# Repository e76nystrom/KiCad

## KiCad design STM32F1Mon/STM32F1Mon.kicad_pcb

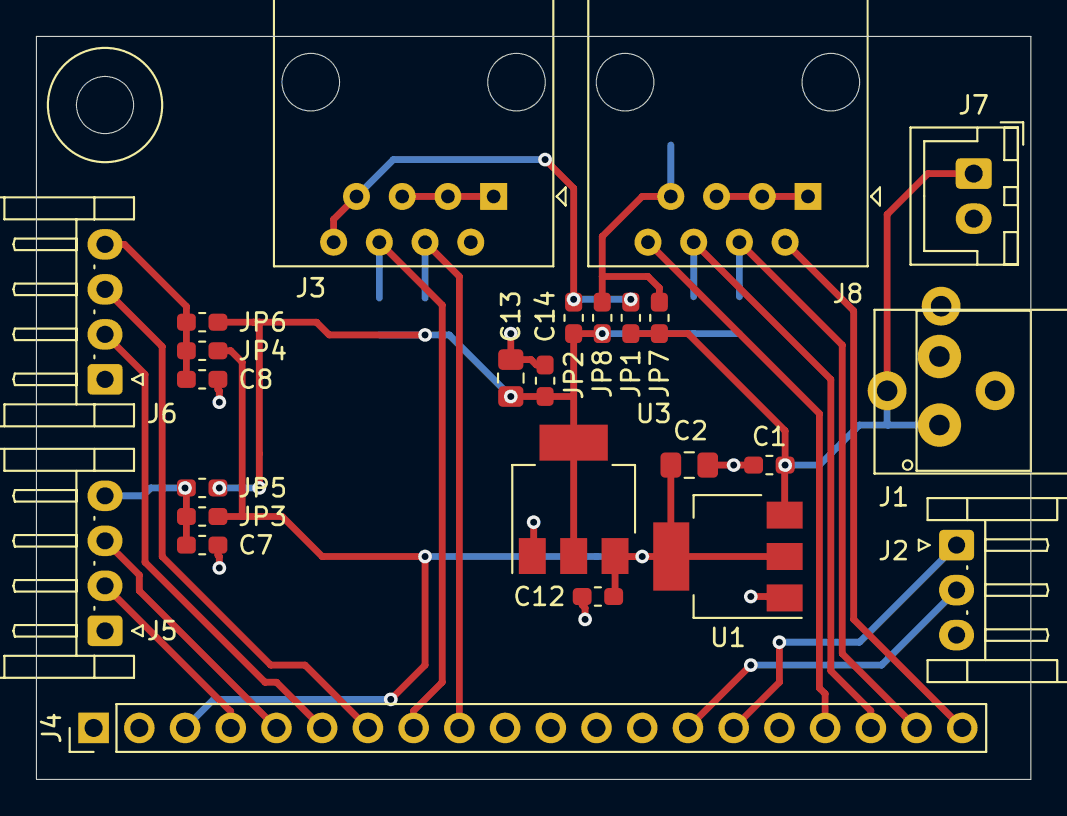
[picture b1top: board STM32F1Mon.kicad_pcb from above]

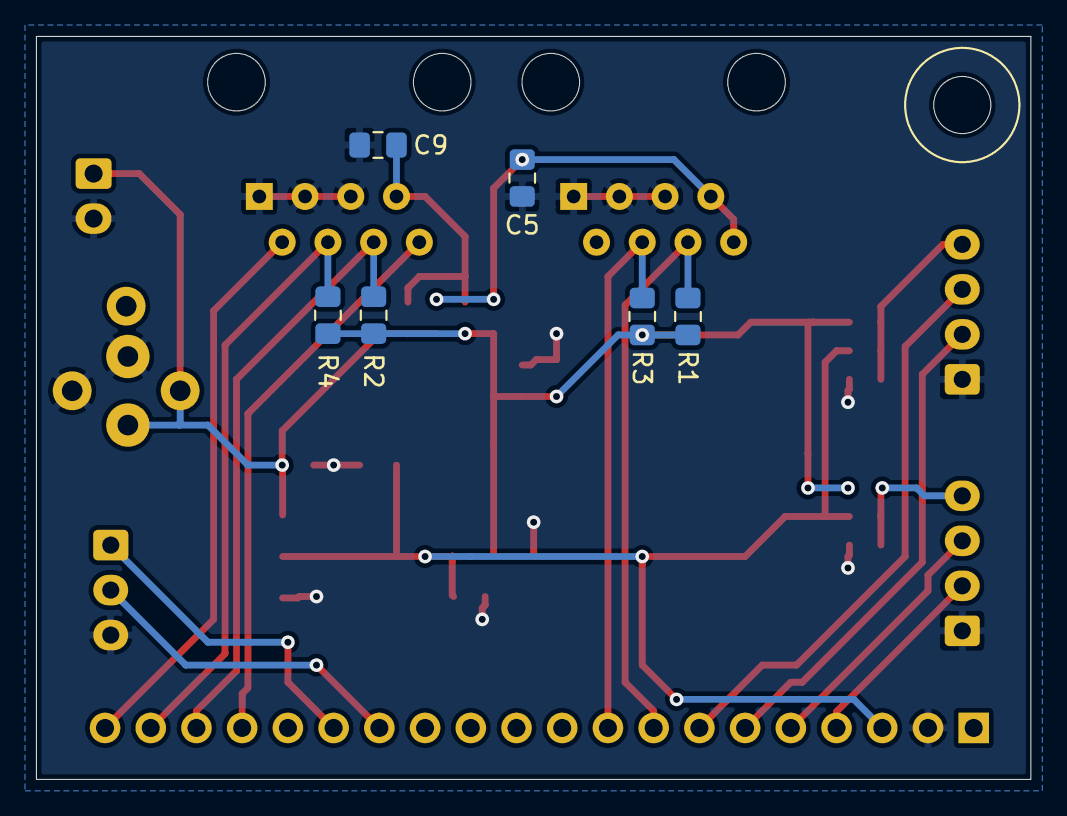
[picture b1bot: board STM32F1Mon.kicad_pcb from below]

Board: 2 copper layers, 55.2 x 41.3 mm, 32 parts (6 on the bottom side), 20 nets.

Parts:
C1, C7, C8, C12, C14: .1uf; C_0603_1608Metric_Pad1.05x0.95mm_HandSolder
C2, C13: 10u; C_0805_2012Metric_Pad1.15x1.40mm_HandSolder
C5, C9: .1; C_0805_2012Metric_Pad1.15x1.40mm_HandSolder
H1: MountingHole; MountingHole _1-8_1-4
J1: PJ-102; PJ-102-3.81mm
J2: Conn_01x03_Female; JST_EH_S3B-EH_1x03_P2.50mm_Horizontal
J3, J8: RJ45; RJ45_Amphenol_54602-x08_Horizontal
J4: Conn_01x20_Male; PinHeader_1x20_P2.54mm_Vertical
J5, J6: Conn_01x04_Female; JST_EH_S4B-EH_1x04_P2.50mm_Horizontal
J7: Conn_01x02; JST_XH_B2B-XH-A_1x02_P2.50mm_Vertical
JP1, JP2, JP3, JP4, JP5, JP6, JP7, JP8: Jumper_NO_Small; R_0603_1608Metric_Pad1.05x0.95mm_HandSolder
R1, R2, R3, R4: R; R_0805_2012Metric_Pad1.15x1.40mm_HandSolder
U1: AP1117-50; SOT-223-3_TabPin2
U3: AP1117-33; SOT-223-3_TabPin2

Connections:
+3V3: C13.1, C14.1, JP2.1, JP5.1, JP6.1, JP8.1, R1.1, R2.1, R3.1, R4.1, U3.2
+5V: C2.1, C12.1, J4.3, JP3.1, JP4.1, U1.2, U3.3
/A9: J2.1, J4.15
/A10: J2.2, J4.14
/B4: J3.4, J4.9, R3.2
/B5: J3.6, J4.8, R1.2
/B6: J4.7, J6.3
/B7: J4.6, J6.2
/B8: J4.5, J5.3
/B9: J4.4, J5.2
/B12: J4.20, J8.2
/B13: J4.19, J8.4, R4.2
/B14: J4.18, J8.6, R2.2
/B15: J4.17, J8.8
/SensorPwr0: C5.1, J3.7, J3.8, JP1.2, JP2.2
/SensorPwr1: C9.1, J8.7, JP7.2, JP8.2
/VA0: C7.2, J5.4, JP3.2, JP5.2
/VA1: C8.2, J6.4, JP4.2, JP6.2
/Vin: C1.1, J1.1, J7.1, JP1.1, JP7.1, U1.3
GND: C1.2, C2.2, C5.2, C7.1, C8.1, C9.2, C12.2, C13.2, C14.2, J1.2, J2.3, J3.1, J3.3, J3.5, J4.2, J5.1, J6.1, J7.2, J8.1, J8.3, J8.5, U1.1, U3.1

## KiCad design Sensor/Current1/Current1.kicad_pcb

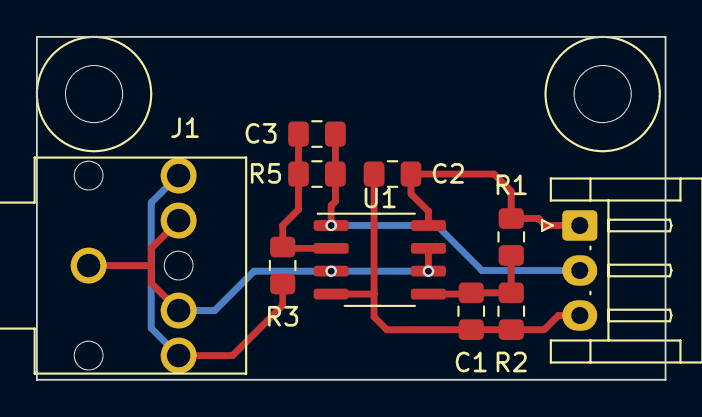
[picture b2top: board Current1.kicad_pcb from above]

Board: 2 copper layers, 34.9 x 19.0 mm, 12 parts (0 on the bottom side), 7 nets.

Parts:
C1: 1uf; C_0805_2012Metric_Pad1.15x1.40mm_HandSolder
C2: .1uf; C_0805_2012Metric_Pad1.15x1.40mm_HandSolder
C3: C; C_0805_2012Metric_Pad1.15x1.40mm_HandSolder
H1, H2: MountingHole; MountingHole _1-8_1-4
J1: STX-3120-5B; AudioJack
J2: Conn_01x03_Male; JST_EH_S3B-EH_1x03_P2.50mm_Horizontal
R1, R2: 10k; R_0805_2012Metric_Pad1.15x1.40mm_HandSolder
R3, R5: R_0805_2012Metric_Pad1.15x1.40mm_HandSolder
U1: OPA2170; SOIC-8_3.9x5.4mm_P1.27mm

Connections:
+3V3: C2.1, J2.1, R1.2, U1.8
/Amp+: J1.1, J1.3, J1.4, U1.3, U1.6, U1.7
/Amp-: C3.2, R3.1, R5.2, U1.2
/Cur+: J1.2, J1.5, R3.2
/Out: C3.1, J2.2, R5.1, U1.1
/Ref: C1.1, R1.1, R2.2, U1.5
GND: C1.2, C2.2, J2.3, R2.1, U1.4

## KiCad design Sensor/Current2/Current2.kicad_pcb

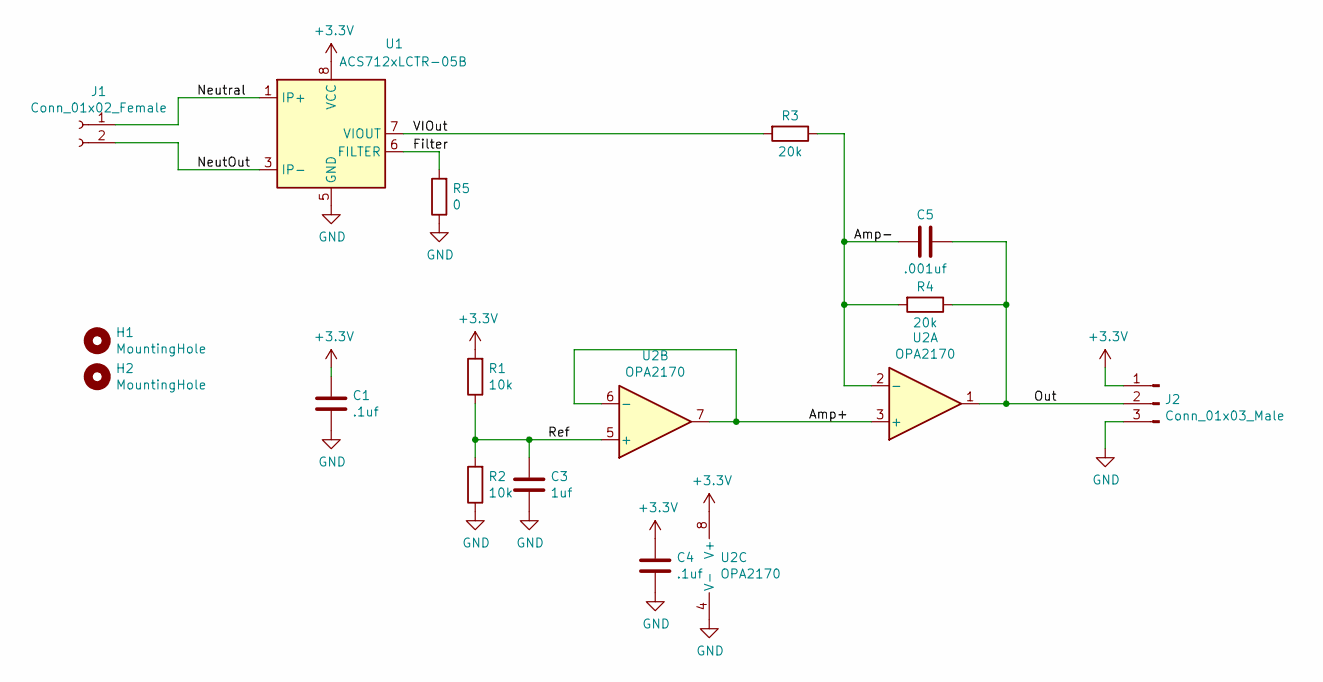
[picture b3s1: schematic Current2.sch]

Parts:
C1, C4: .1uf; C_0805_2012Metric_Pad1.15x1.40mm_HandSolder
C3: 1uf; C_0805_2012Metric_Pad1.15x1.40mm_HandSolder
C5: .001uf; C_0805_2012Metric_Pad1.15x1.40mm_HandSolder
H1, H2: MountingHole; MountingHole _1-8_1-4
J1: Conn_01x02_Female; 2_Pin_5mm
J2: Conn_01x03_Male; JST_EH_S3B-EH_1x03_P2.50mm_Horizontal
R1, R2: 10k; R_0805_2012Metric_Pad1.15x1.40mm_HandSolder
R3, R4: 20k; R_0805_2012Metric_Pad1.15x1.40mm_HandSolder
R5: 0; R_0805_2012Metric_Pad1.15x1.40mm_HandSolder
U1: ACS712xLCTR-05B; SOIC-8_3.9x5.6mm_P1.27mm
U2: OPA2170; SOIC-8_3.9x5.4mm_P1.27mm

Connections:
+3V3: C1.1, C4.1, J2.1, R1.2, U1.8 (VCC), U2.8 (V+)
/Amp+: U2.3 (+), U2.6 (-), U2.7
/Amp-: C5.2, R3.1, R4.2, U2.2 (-)
/Filter: R5.2, U1.6 (FILTER)
/NeutOut: J1.2, U1.3 (IP-), U1.4 (IP-)
/Neutral: J1.1, U1.1 (IP+), U1.2 (IP+)
/Out: C5.1, J2.2, R4.1, U2.1
/Ref: C3.1, R1.1, R2.2, U2.5 (+)
/VIOut: R3.2, U1.7 (VIOUT)
GND: C1.2, C3.2, C4.2, J2.3, R2.1, R5.1, U1.5 (GND), U2.4 (V-)

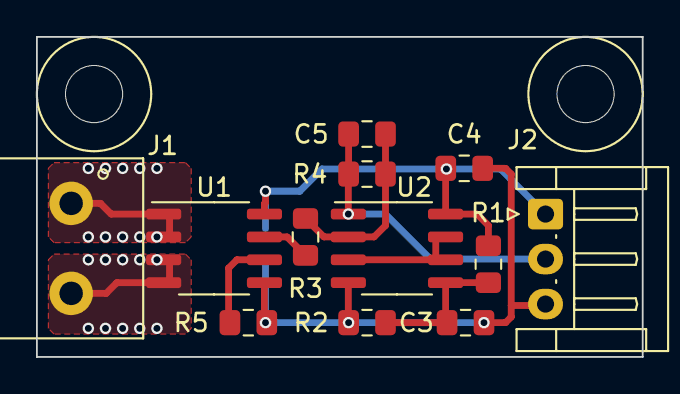
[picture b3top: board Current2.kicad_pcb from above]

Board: 2 copper layers, 33.7 x 17.8 mm, 15 parts (1 on the bottom side), 10 nets.

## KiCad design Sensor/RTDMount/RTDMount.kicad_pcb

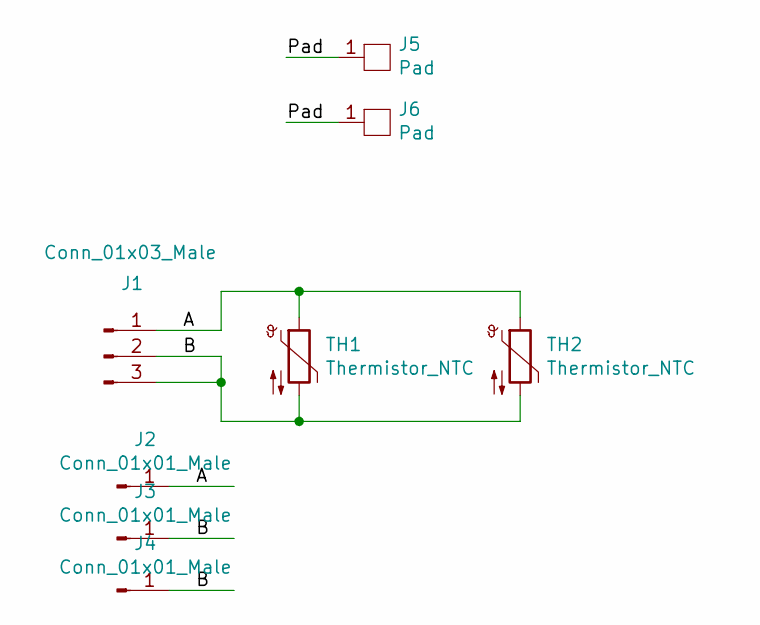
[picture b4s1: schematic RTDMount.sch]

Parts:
J1: Conn_01x03_Male; JST_EH_S3B-EH_1x03_P2.50mm_Horizontal
J2, J3, J4: Conn_01x01_Male; RectPad-025x100
J5, J6: Pad; SurfaceMountPad
TH1: Thermistor_NTC; RTD
TH2: Thermistor_NTC; R_0603_1608Metric_Pad1.05x0.95mm_HandSolder

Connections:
/A: J1.1, J2.1, TH1.1, TH2.1
/B: J1.2, J1.3, J3.1, J4.1, TH1.2, TH2.2
/Pad: J5.1, J6.1

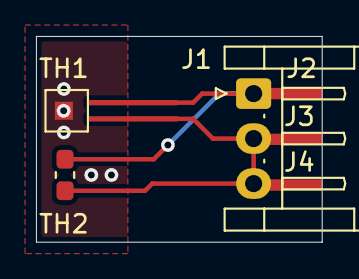
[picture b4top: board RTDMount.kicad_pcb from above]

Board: 2 copper layers, 15.9 x 11.4 mm, 8 parts (1 on the bottom side), 3 nets.

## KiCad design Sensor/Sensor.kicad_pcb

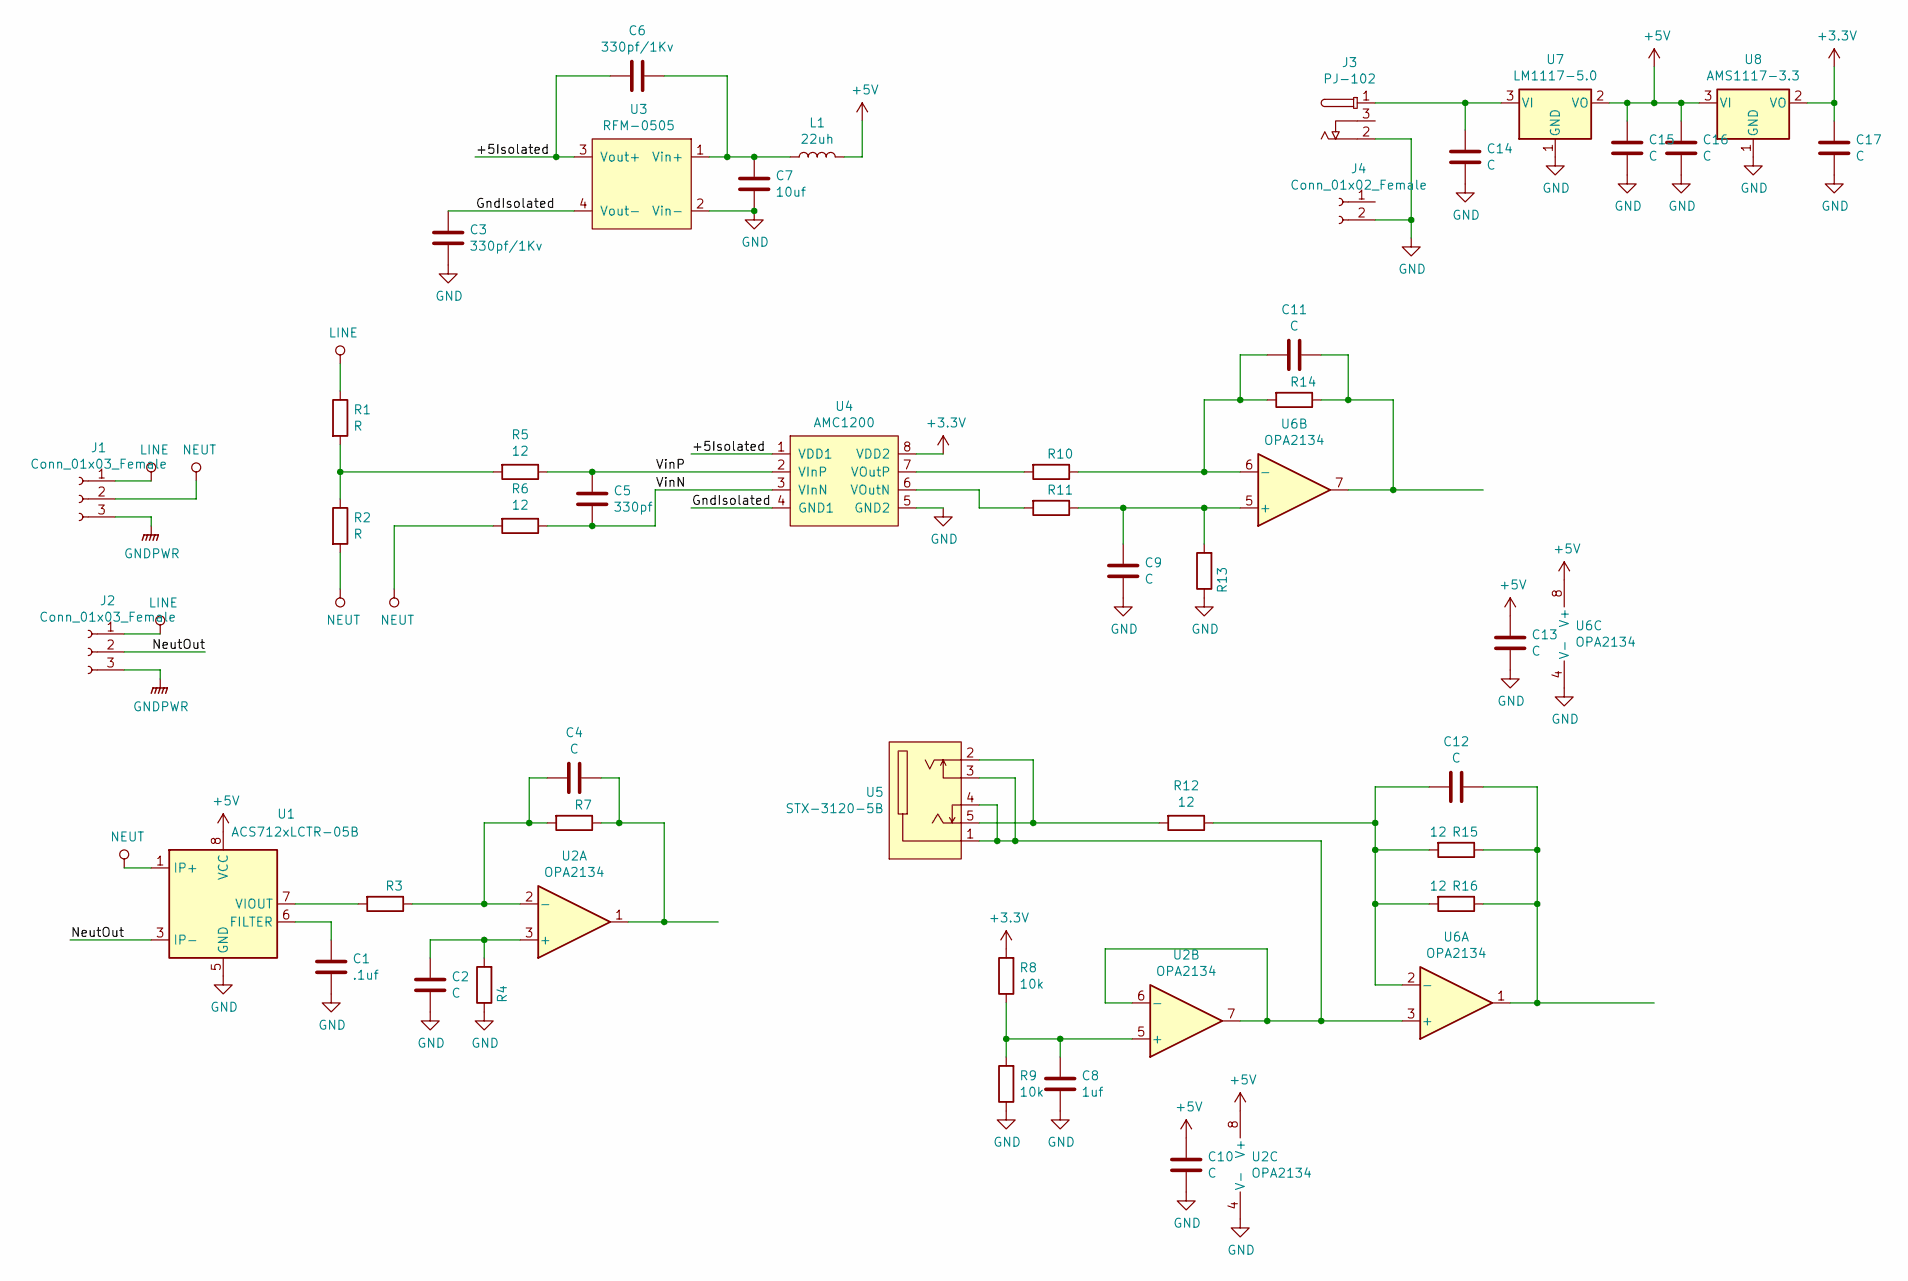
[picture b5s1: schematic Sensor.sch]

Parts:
C1: .1uf; C_0805_2012Metric_Pad1.15x1.40mm_HandSolder
C2, C4, C9, C10, C11, C12, C13, C14, C15, C16, C17: C; C_0805_2012Metric_Pad1.15x1.40mm_HandSolder
C3, C6: 330pf/1Kv; C_Rect_L11.6mm_W4.1mm_P6.00mm_MKT
C5: 330pf; C_1210_3225Metric
C7: 10uf; C_0805_2012Metric_Pad1.15x1.40mm_HandSolder
C8: 1uf; C_0805_2012Metric_Pad1.15x1.40mm_HandSolder
J1, J2: Conn_01x03_Female; 3_Pin_3.81mm
J3: PJ-102
J4: Conn_01x02_Female; 2 Pin 3.81mm
L1: 22uh; L_0805_2012Metric_Pad1.15x1.40mm_HandSolder
R1, R2: R; R_0805_2012Metric_Pad1.15x1.40mm_HandSolder
R3, R4, R7, R10, R11, R13, R14: R_0805_2012Metric_Pad1.15x1.40mm_HandSolder
R5, R6: 12; R_0603_1608Metric_Pad1.05x0.95mm_HandSolder
R8, R9: 10k; R_0805_2012Metric_Pad1.15x1.40mm_HandSolder
R12, R15, R16: 12; R_0805_2012Metric_Pad1.15x1.40mm_HandSolder
U1: ACS712xLCTR-05B; SOIC-8_3.9x4.9mm_P1.27mm
U2, U6: OPA2134; SOIC-8_3.9x4.9mm_P1.27mm
U3: RFM-0505; RFM
U4: AMC1200; SOIC-8_AMC1200
U5: STX-3120-5B; AudioJack
U7: LM1117-5.0; SOT-223-3_TabPin2
U8: AMS1117-3.3; SOT-89-3_Handsoldering

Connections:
+3V3: C17.1, R8.2, U4.8 (VDD2), U8.2 (VO)
+5V: C10.1, C13.1, C15.1, C16.1, L1.2, U1.8 (VCC), U2.8 (V+), U6.8 (V+), U7.2 (VO), U8.3 (VI)
/+5Isolated: C6.2, U3.3 (Vout+), U4.1 (VDD1)
/GndIsolated: C3.1, U3.4 (Vout-), U4.4 (GND1)
/NeutOut: J2.2, U1.3 (IP-), U1.4 (IP-)
/VinN: C5.2, R6.1, U4.3 (VInN)
/VinP: C5.1, R5.1, U4.2 (VInP)
GND: C1.2, C2.2, C3.2, C7.2, C8.2, C9.2, C10.2, C13.2, C14.2, C15.2, C16.2, C17.2, J3.2, J4.2, R4.1, R9.1, R13.1, U1.5 (GND), U2.4 (V-), U3.2 (Vin-), U4.5 (GND2), U6.4 (V-), U7.1 (GND), U8.1 (GND)
GNDPWR: J1.3, J2.3
LINE: J1.1, J2.1, R1.1
NEUT: J1.2, R2.2, R6.2, U1.1 (IP+), U1.2 (IP+)
unnamed: C1.1, U1.6 (FILTER)
unnamed: C2.1, R4.2, U2.3 (+)
unnamed: C4.1, R7.1, U2.1
unnamed: C4.2, R3.1, R7.2, U2.2 (-)
unnamed: C6.1, C7.1, L1.1, U3.1 (Vin+)
unnamed: C8.1, R8.1, R9.2, U2.5 (+)
unnamed: C9.1, R11.1, R13.2, U6.5 (+)
unnamed: C11.1, R14.1, U6.7
unnamed: C11.2, R10.1, R14.2, U6.6 (-)
unnamed: C12.1, R15.1, R16.1, U6.1
unnamed: C12.2, R12.1, R15.2, R16.2, U6.2 (-)
unnamed: C14.1, J3.1, U7.3 (VI)
unnamed: R1.2, R2.1, R5.2
unnamed: R3.2, U1.7 (VIOUT)
unnamed: R10.2, U4.7 (VOutP)
unnamed: R11.2, U4.6 (VOutN)
unnamed: R12.2, U5.2, U5.5
unnamed: U2.6 (-), U2.7, U5.1, U5.3, U5.4, U6.3 (+)

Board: 2 copper layers, 46 parts (0 on the bottom side), 29 nets, no tracks yet.

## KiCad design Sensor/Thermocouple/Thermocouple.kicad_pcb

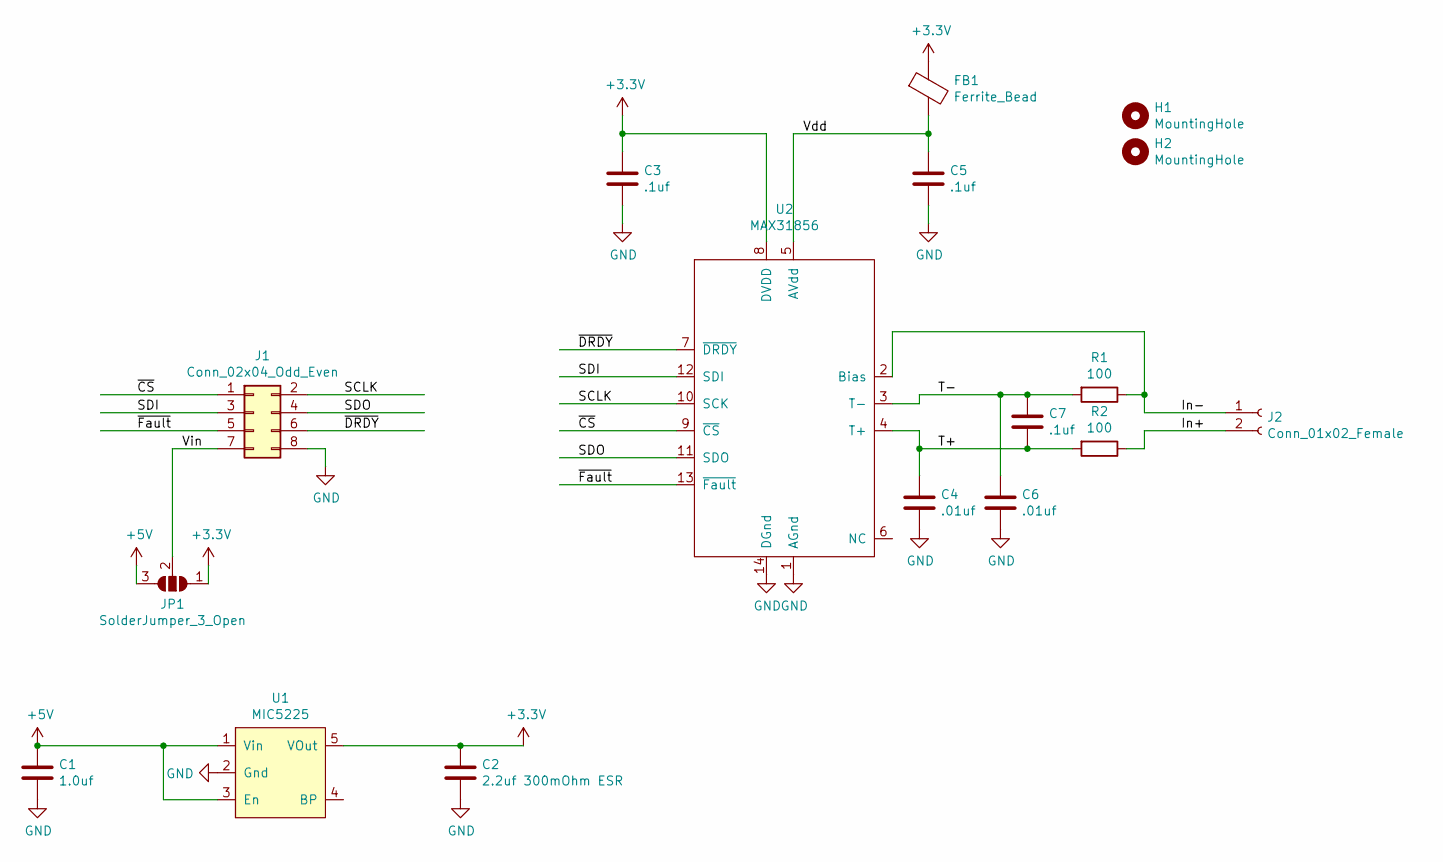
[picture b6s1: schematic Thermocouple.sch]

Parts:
C1: 1.0uf; C_0805_2012Metric_Pad1.15x1.40mm_HandSolder
C2: 2.2uf 300mOhm ESR; C_0805_2012Metric_Pad1.15x1.40mm_HandSolder
C3, C5, C7: .1uf; C_0805_2012Metric_Pad1.15x1.40mm_HandSolder
C4, C6: .01uf; C_0805_2012Metric_Pad1.15x1.40mm_HandSolder
FB1: Ferrite_Bead; L_0805_2012Metric_Pad1.15x1.40mm_HandSolder
H1, H2: MountingHole; MountingHole _1-8_1-4
J1: Conn_02x04_Odd_Even; PinHeader_2x04_P2.54mm_Vertical
J2: Conn_01x02_Female; PhoenixContact_MC_1,5_2-G-3.81_1x02_P3.81mm_Horizontal
JP1: SolderJumper_3_Open; Jumper_0805_3
R1, R2: 100; R_0805_2012Metric_Pad1.15x1.40mm_HandSolder
U1: MIC5225; SOT-23-5_HandSoldering
U2: MAX31856; TSSOP-14_4.4x5mm_P0.65mm_MAX

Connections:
+3V3: C2.1, C3.1, FB1.1, JP1.1 (A), U1.5 (VOut), U2.8 (DVDD)
+5V: C1.1, JP1.3 (B), U1.1 (Vin), U1.3 (En)
/In+: J2.2, R2.1
/In-: J2.1, R1.1, U2.2 (Bias)
/SCLK: J1.2, U2.10 (SCK)
/SDI: J1.3, U2.12 (SDI)
/SDO: J1.4, U2.11 (SDO)
/T+: C4.1, C7.2, R2.2, U2.4 (T+)
/T-: C6.1, C7.1, R1.2, U2.3 (T-)
/Vdd: C5.2, FB1.2, U2.5 (AVdd)
/Vin: J1.7, JP1.2 (C)
/~CS: J1.1, U2.9 (~CS)
/~DRDY: J1.6, U2.7 (~DRDY)
/~Fault: J1.5, U2.13 (~Fault)
GND: C1.2, C2.2, C3.2, C4.2, C5.1, C6.2, J1.8, U1.2 (Gnd), U2.1 (AGnd), U2.14 (DGnd)

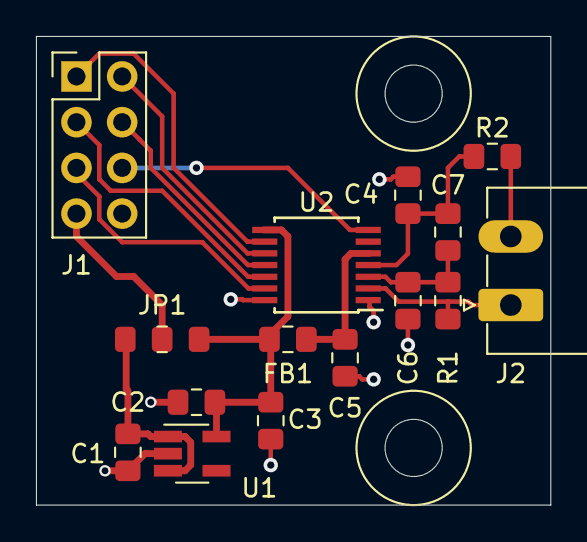
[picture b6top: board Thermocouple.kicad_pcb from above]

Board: 2 copper layers, 28.6 x 26.0 mm, 17 parts (0 on the bottom side), 15 nets.

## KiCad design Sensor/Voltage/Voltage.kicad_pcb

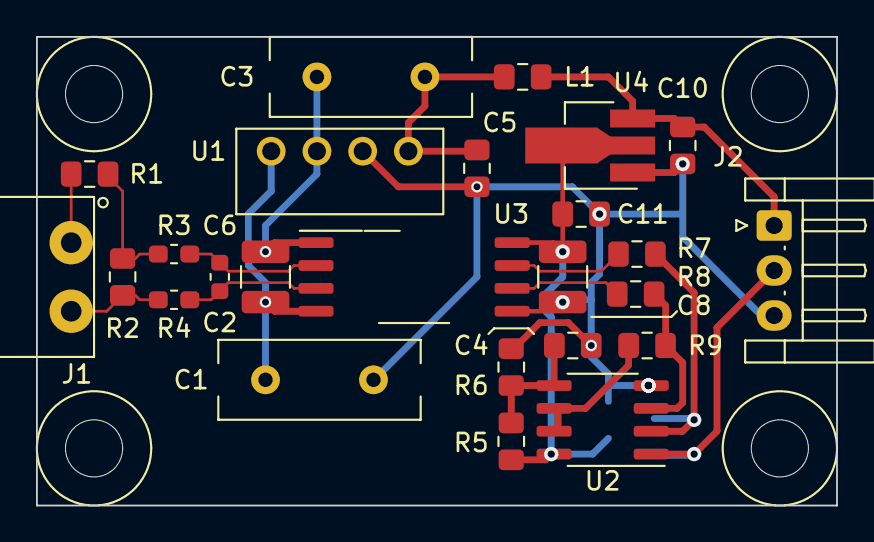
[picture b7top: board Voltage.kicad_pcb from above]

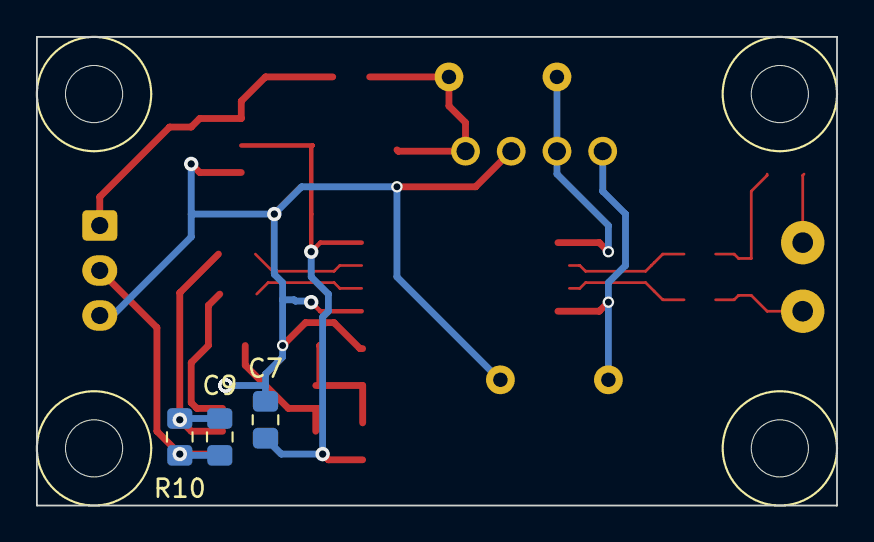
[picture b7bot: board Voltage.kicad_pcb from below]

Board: 2 copper layers, 44.5 x 26.0 mm, 32 parts (3 on the bottom side), 18 nets.

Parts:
C1, C3: 330pf/1Kv; C_Rect_L11.6mm_W4.1mm_P6.00mm_MKT
C2: 330pf; C_0603_1608Metric
C4: 1uf; C_0805_2012Metric_Pad1.15x1.40mm_HandSolder
C5: 10uf; C_0805_2012Metric_Pad1.15x1.40mm_HandSolder
C6, C8: .1uf; C_1210_3225Metric
C7: .1uf; C_0805_2012Metric_Pad1.15x1.40mm_HandSolder
C9, C10, C11: C; C_0805_2012Metric_Pad1.15x1.40mm_HandSolder
H1, H2, H3, H4: MountingHole; MountingHole _1-8_1-4
J1: Conn_01x02_Female; 2 Pin 3.81mm
J2: Conn_01x03_Male; JST_EH_S3B-EH_1x03_P2.50mm_Horizontal
L1: 22uh; L_0805_2012Metric_Pad1.15x1.40mm_HandSolder
R1, R2: R; R_0805_2012Metric_Pad1.15x1.40mm_HandSolder
R3, R4: 12; R_0603_1608Metric_Pad1.05x0.95mm_HandSolder
R5, R6, R9: 10k; R_0805_2012Metric_Pad1.15x1.40mm_HandSolder
R7, R8, R10: R_0805_2012Metric_Pad1.15x1.40mm_HandSolder
U1: RFM-0505; RFM
U2: OPA2134; SOIC-8_3.9x5.4mm_P1.27mm
U3: AMC1200; SOIC-8_AMC1200
U4: AMS1117-3.3; SOT-89-3_Handsoldering

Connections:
+3V3: C7.1, C8.1, C11.1, R5.2, U2.8, U3.8, U4.2
+5V: C10.1, J2.1, L1.2, U4.3
/+5Isolated: C3.2, C6.1, U1.3, U3.1
/Amp+: R8.1, R9.2, U2.3
/Amp-: C9.2, R7.1, R10.2, U2.2
/GndIsolated: C1.1, C6.2, U1.4, U3.4
/Out: C9.1, J2.2, R10.1, U2.1
/Ref: C4.1, R5.1, R6.2, U2.5
/RefOut: R9.1, U2.6, U2.7
/VDConv: C3.1, C5.1, L1.1, U1.1
/VDiv: R1.2, R2.1, R3.2
/VOutN: R8.2, U3.6
/VOutP: R7.2, U3.7
/VinN: C2.2, R4.1, U3.3
/VinP: C2.1, R3.1, U3.2
GND: C1.2, C4.2, C5.2, C7.2, C8.2, C10.2, C11.2, J2.3, R6.1, U1.2, U2.4, U3.5, U4.1
LINE: J1.1, R1.1
NEUT: J1.2, R2.2, R4.2

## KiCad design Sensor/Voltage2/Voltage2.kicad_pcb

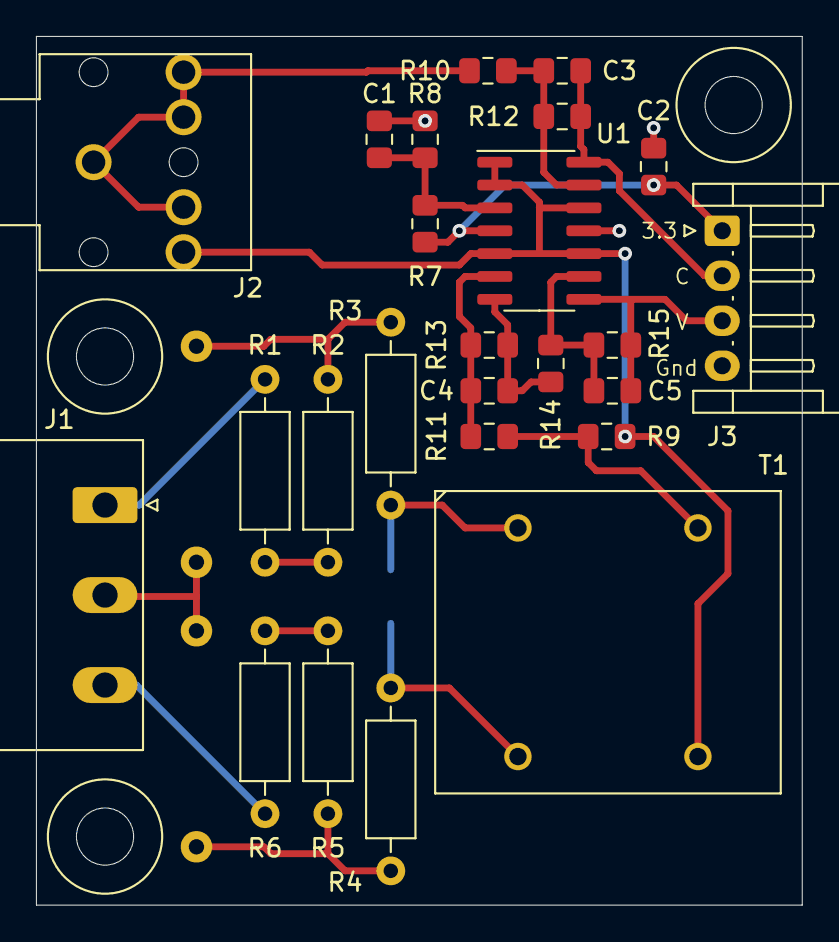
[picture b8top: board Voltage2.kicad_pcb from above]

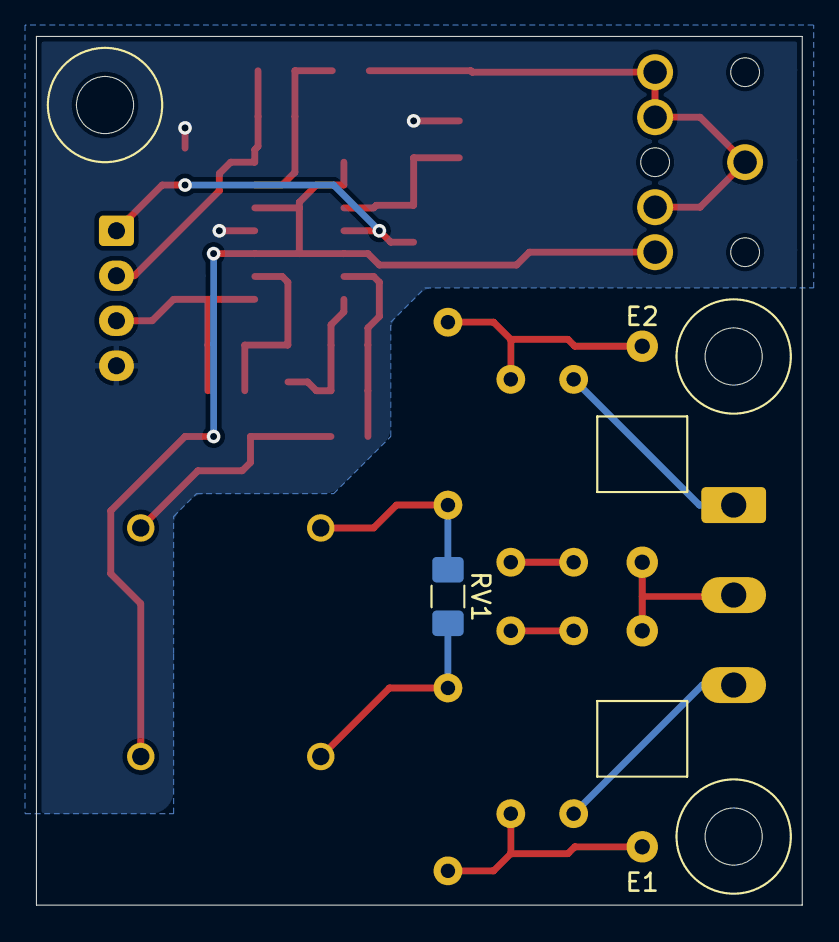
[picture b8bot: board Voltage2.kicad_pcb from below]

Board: 2 copper layers, 42.5 x 48.3 mm, 31 parts (3 on the bottom side), 21 nets.

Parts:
C1: 1uf; C_0805_2012Metric_Pad1.15x1.40mm_HandSolder
C2: .1uf; C_0805_2012Metric_Pad1.15x1.40mm_HandSolder
C3: C; C_0805_2012Metric_Pad1.15x1.40mm_HandSolder
C4, C5: .001uf; C_0805_2012Metric_Pad1.15x1.40mm_HandSolder
E1, E2: GDT; GDT-2035
H1, H2, H3: MountingHole; MountingHole _1-8_1-4
J1: Conn_01x03_Female; PhoenixContact_MSTBA_2,5_3-G_1x03_P5.00mm_Horizontal
J2: STX-3120-5B; AudioJack
J3: Conn_01x04_Female; JST_EH_S4B-EH_1x04_P2.50mm_Horizontal
R1, R2, R3, R4, R5, R6: 21k; R_Axial_DIN0207_L6.3mm_D2.5mm_P10.16mm_Horizontal
R7, R8: 10k; R_0805_2012Metric_Pad1.15x1.40mm_HandSolder
R9: 100; R_0805_2012Metric_Pad1.15x1.40mm_HandSolder
R10, R12: R_0805_2012Metric_Pad1.15x1.40mm_HandSolder
R11, R14: 20k; R_0805_2012Metric_Pad1.15x1.40mm_HandSolder
R13, R15: 300k; R_0805_2012Metric_Pad1.15x1.40mm_HandSolder
RV1: MOV; R_1206_3216Metric_Pad1.42x1.75mm_HandSolder
T1: Transformer_1P_1S; ZMPT101B
U1: OPA4134; SOIC-14_3.9x8.7mm_P1.27mm

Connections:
+3V3: C2.1, J3.1, R7.2, U1.4
/Amp+: J2.5, R9.1, T1.3, U1.1, U1.2, U1.5, U1.10, U1.12
/AmpC-: C3.2, R10.1, R12.2, U1.13
/AmpV1-: C5.2, R14.1, R15.2, U1.9
/AmpV-: C4.2, R11.1, R13.2, U1.6
/Anp0: C4.1, R13.1, R14.2, U1.7
/COut: C3.1, J3.2, R12.1, U1.14
/Cur+: J2.1, J2.2, J2.3, J2.4, R10.2
/In: R9.2, R11.2, T1.4
/L1: J1.1, R1.1
/L1A: R1.2, R2.1
/L1B: E2.1, R2.2, R3.1
/L1C: R3.2, RV1.1, T1.1
/L2: J1.3, R6.2
/L2A: R5.2, R6.1
/L2B: E1.1, R4.2, R5.1
/L2C: R4.1, RV1.2, T1.2
/Ref: C1.1, R7.1, R8.2, U1.3
/VOut: C5.1, J3.3, R15.1, U1.8
GND: C1.2, C2.2, J3.4, R8.1, U1.11
GNDPWR: E1.2, E2.2, J1.2
